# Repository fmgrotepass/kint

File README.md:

# Project moved to [Pillz Mod](https://github.com/dcpedit/pillzmod)

This project has been replaced by Pillz Mod: https://github.com/dcpedit/pillzmod

# KinT Blackpill Edition

This is a fork of Michael Stapelberg's [KinT project](https://github.com/kinx-project/kint) with the following modifications:

* Replaced Teensy with STM32F411 Blackpill controller (`blackpill` directory)
* Reduced PCB size to 100 x 86 mm
* Use Vial firmware.  Source code is in my [fork of Vial](https://github.com/dcpedit/vial-qmk-dev/tree/vial/keyboards/dcpedit/kint_bp)

## Files for JLCPCB
Located in the directory `/blackpill/production`

## Parts for Build
| Component              | Qty | Notes |
| ---------              | --- | ----- |
| SMD LEDs               | 4   | Can be any color [Link](https://octopart.com/apt3216qbc%2Fd-kingbright-5355642?r=sp)
| SMD 10k resistors      | 4   | [Link](https://octopart.com/crcw120610k0fkeac-vishay-20811529)
| Molex 13 pin connectors| 4-6 | Needed if you don't want to desolder old ones [Link](https://octopart.com/39-53-2135-molex-7670149?r=sp)
| STM32F411 Blackpill    | 1   | AliExpress [Link](https://www.aliexpress.us/item/3256801269871873.html)
| Panel mount USB-C      | 1   | Amazon [Link](https://a.co/d/cRoqHqx)
| Socketed headers       |     | Only needed if you want to socket your Blackpill.

## Bluetooth + ZMK build
You can now use the Pillbug dev board along with ZMK firware to make this a wireless mod.  Basically, just swap out the Blackpill with a Pillbug and add a battery.

| Component              | Qty | Notes |
| ---------              | --- | ----- |
| Pillbug                | 1   | MechWild [Link](https://mechwild.com/product/pillbug/)
| 2000 mAh battery       | 1   | Amazon [Link](https://a.co/d/hlTVT1p)

v2022-08-05 of the PCB requires you to bridge the 3.3v pins with a wire.  You can do this easily after soldering the controller in place and tacking a short wire with stripped ends to the existing solder joints on the same side as the LEDs/resistors.  The diagram below shows you which pins.

The current version in the repo does not require this.

If you're using a battery that's larger than 500 mAh, short JP1 on the back of the Pillbug to enable "Charge Boost" (changes charge rate from 100mA to 500mA)

## Firmware
### Vial
Source: https://github.com/dcpedit/vial-qmk-dev/tree/vial/keyboards/dcpedit/kint_bp
* `/firmware/dcpedit_kint_bp_vial.bin` - Default keymap (stock Kinesis)
* `/firmware/dcpedit_kint_bp_vial_6layers.bin` - Support for 6 layers

### ZMK
Source: https://github.com/dcpedit/zmk/tree/kinesispb/app/boards/shields/kinesispb
* `/firmware/zmk_default.uf2` - Default keymap (stock Kinesis)
* `/firmware/zmk_reset.uf2` - Resets PillBug board for BT connectivity issue on MacOS

### Flashing firmware under Linux
The file firmware/dcpedit_kint_bp_vial.bin (or other) can simply be flashed to the Blackpill using the dfu_util. The dfu_util tool requires root privileges if settings are not accessible by the user.

Connect Blackpill to your Linux PC via USB C cable and start unit in DFU mode by holding bootp button and pressing reset button. Wait a second and release the bootp button.

Check the DFU devices by running
```
dfu-util -l
```
The Blackpill device should be visible.

Write the firmware to the device with
```
dfu-util -d 0483:df11 -a 0 -s 0x08000000 -D [PATH TO kint]/firmware/dcpedit_kint_bp_vial.bin
```

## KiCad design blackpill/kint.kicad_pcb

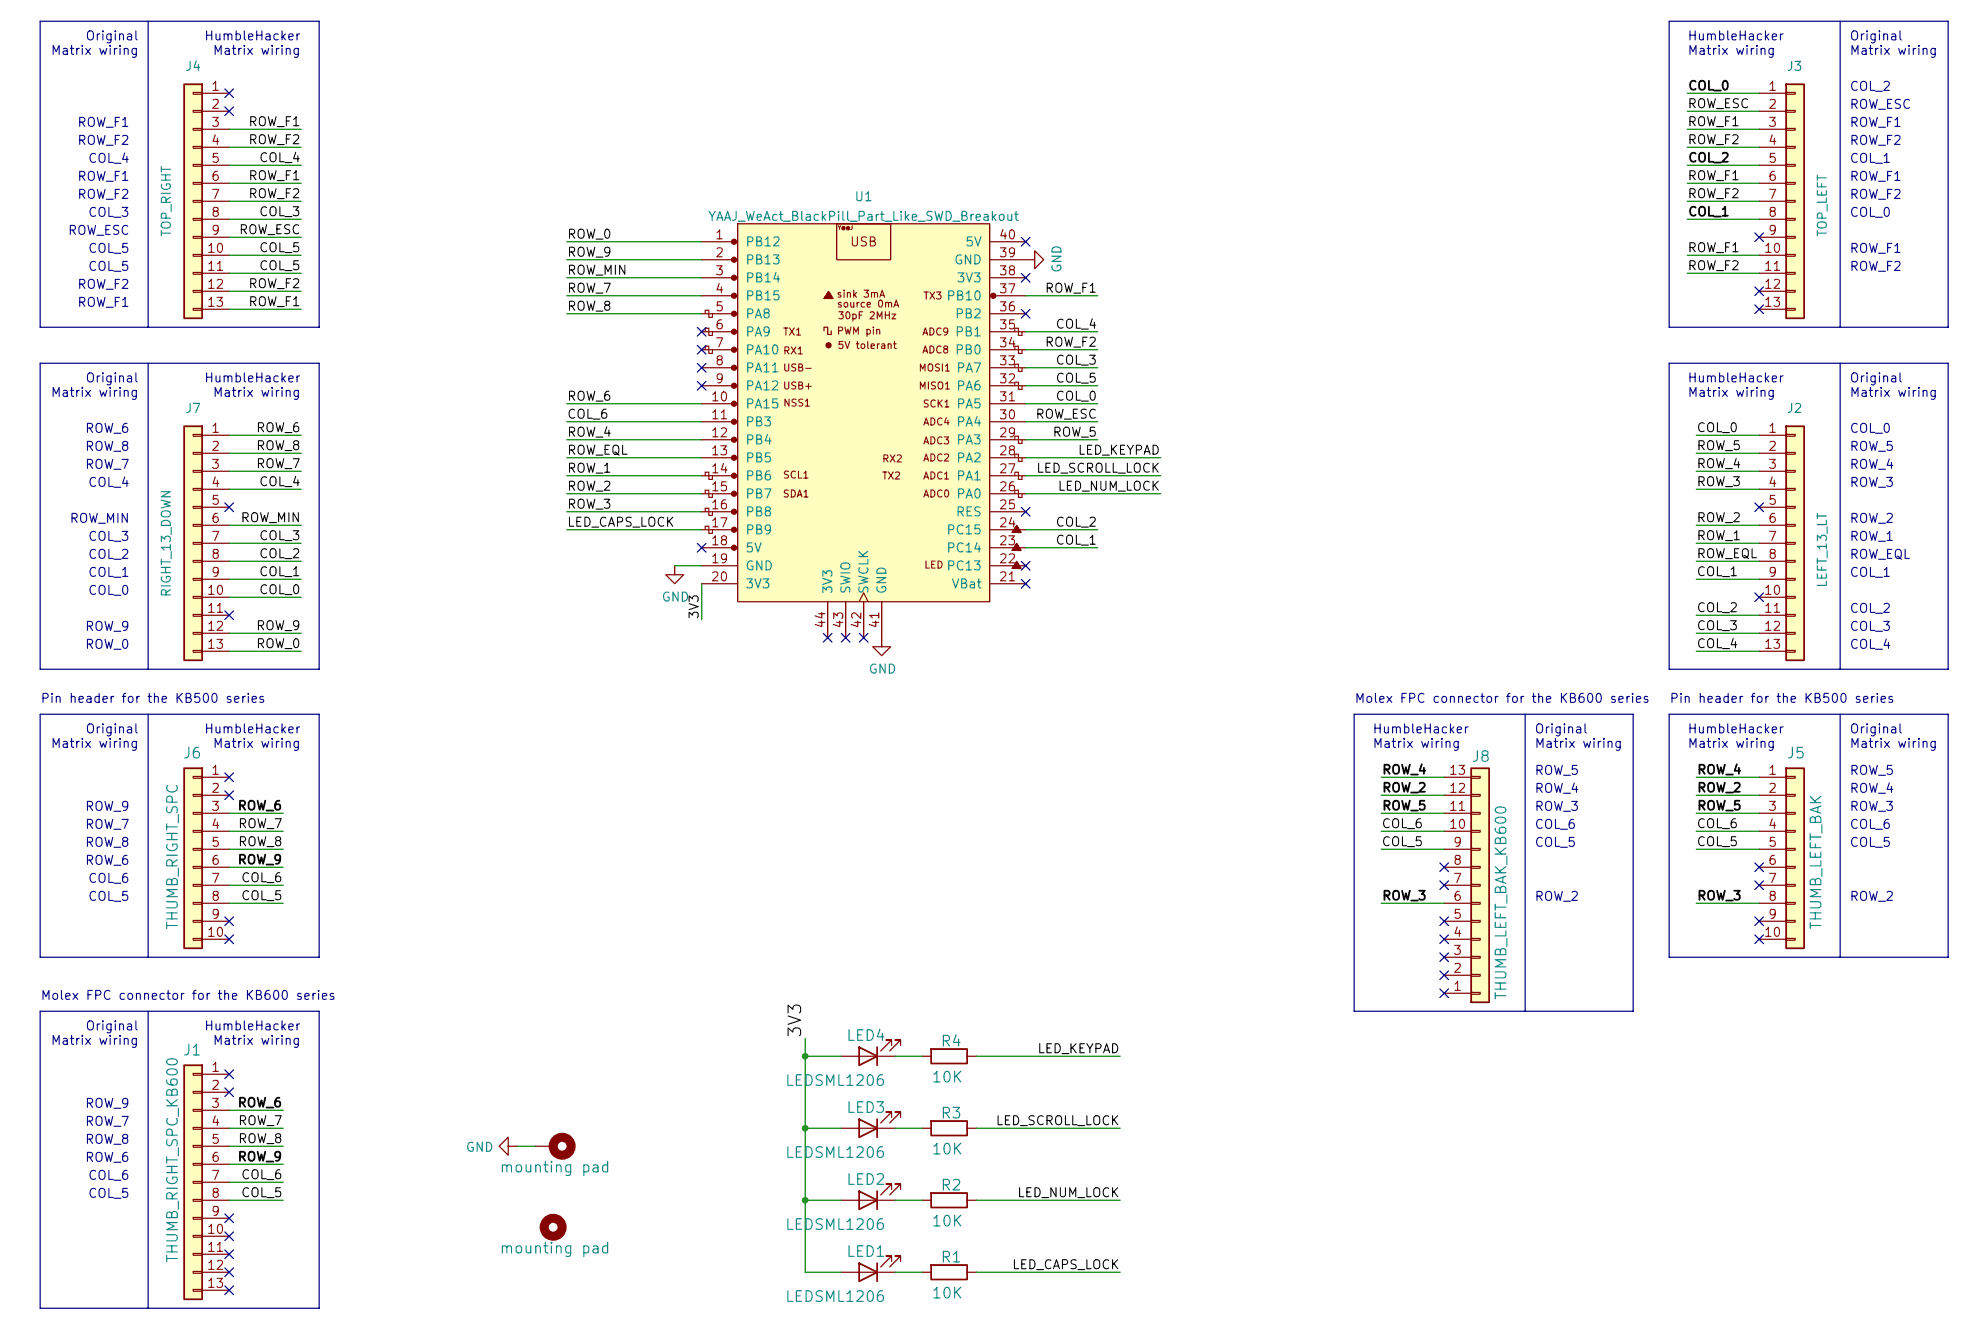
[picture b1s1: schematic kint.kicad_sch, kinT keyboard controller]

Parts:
H1: mounting pad; MountingHole_4.3mm_M4_Pad
H2: mounting pad; MountingHole_6mm
J1: THUMB_RIGHT_SPC_KB600; 39-53-2135; MPN 39-53-2135; digikeypn WM14526-ND
J2: LEFT_13_LT; 39-53-2135; MPN 39-53-2135; digikeypn WM14526-ND
J3: TOP_LEFT; 39-53-2135; MPN 39-53-2135; digikeypn WM14526-ND
J4: TOP_RIGHT; 39-53-2135; MPN 39-53-2135; digikeypn WM14526-ND
J5: THUMB_LEFT_BAK; PinHeader_1x10_P2.54mm_Vertical; MPN 39-53-2135; digikeypn WM14526-ND
J6: THUMB_RIGHT_SPC; PinHeader_1x10_P2.54mm_Vertical; MPN 39-53-2135; digikeypn WM14526-ND
J7: RIGHT_13_DOWN; 39-53-2135; MPN 39-53-2135; digikeypn WM14526-ND
J8: THUMB_LEFT_BAK_KB600; 39-53-2135; MPN 39-53-2135; digikeypn WM14526-ND
LED1, LED2, LED3, LED4: LEDSML1206; LED_1206_3216Metric_Pad1.42x1.75mm_HandSolder; MPN APT3216QBC/D; digikeypn 754-1439-1-ND
R1, R2, R3, R4: 10K; R_1206_3216Metric_Pad1.42x1.75mm_HandSolder; MPN CRCW120610K0FKEAC; digikeypn 541-3983-1-ND
U1: YAAJ_WeAct_BlackPill_Part_Like_SWD_Breakout; YAAJ_WeAct_BlackPill_SWD_2

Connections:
/3V3: LED1.2 (A), LED2.2 (A), LED3.2 (A), LED4.2 (A), U1.20 (3V3)
/COL_0: J2.1, J3.1, J7.10, U1.31 (PA5)
/COL_1: J2.9, J3.8, J7.9, U1.23 (PC14)
/COL_2: J2.11, J3.5, J7.8, U1.24 (PC15)
/COL_3: J2.12, J4.8, J7.7, U1.33 (PA7)
/COL_4: J2.13, J4.5, J7.4, U1.35 (PB1)
/COL_5: J1.8, J4.10, J4.11, J5.5, J6.8, J8.9, U1.32 (PA6)
/COL_6: J1.7, J5.4, J6.7, J8.10, U1.11 (PB3)
/LED_CAPS_LOCK: R1.1, U1.17 (PB9)
/LED_KEYPAD: R4.1, U1.28 (PA2)
/LED_NUM_LOCK: R2.1, U1.26 (PA0)
/LED_SCROLL_LOCK: R3.1, U1.27 (PA1)
/ROW_0: J7.13, U1.1 (PB12)
/ROW_1: J2.7, U1.14 (PB6)
/ROW_2: J2.6, J5.2, J8.12, U1.15 (PB7)
/ROW_3: J2.4, J5.8, J8.6, U1.16 (PB8)
/ROW_4: J2.3, J5.1, J8.13, U1.12 (PB4)
/ROW_5: J2.2, J5.3, J8.11, U1.29 (PA3)
/ROW_6: J1.3, J6.3, J7.1, U1.10 (PA15)
/ROW_7: J1.4, J6.4, J7.3, U1.4 (PB15)
/ROW_8: J1.5, J6.5, J7.2, U1.5 (PA8)
/ROW_9: J1.6, J6.6, J7.12, U1.2 (PB13)
/ROW_EQL: J2.8, U1.13 (PB5)
/ROW_ESC: J3.2, J4.9, U1.30 (PA4)
/ROW_F1: J3.3, J3.6, J3.10, J4.3, J4.6, J4.13, U1.37 (PB10)
/ROW_F2: J3.4, J3.7, J3.11, J4.4, J4.7, J4.12, U1.34 (PB0)
/ROW_MIN: J7.6, U1.3 (PB14)
GND: H1.1, U1.19 (GND), U1.39 (GND), U1.41 (GND)
unnamed: LED1.1 (K), R1.2
unnamed: LED2.1 (K), R2.2
unnamed: LED3.1 (K), R3.2
unnamed: LED4.1 (K), R4.2

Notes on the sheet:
COL_6
ROW_F2
ROW_6
Pin header for the KB500 series
Molex FPC connector for the KB600 series
ROW_7
COL_3
ROW_4
ROW_ESC
COL_0
ROW_3
ROW_2
ROW_1
Original Matrix wiring
ROW_5
ROW_MIN
ROW_F1
HumbleHacker Matrix wiring
ROW_EQL
ROW_9
COL_4
COL_5
COL_1
COL_2
ROW_8
ROW_0

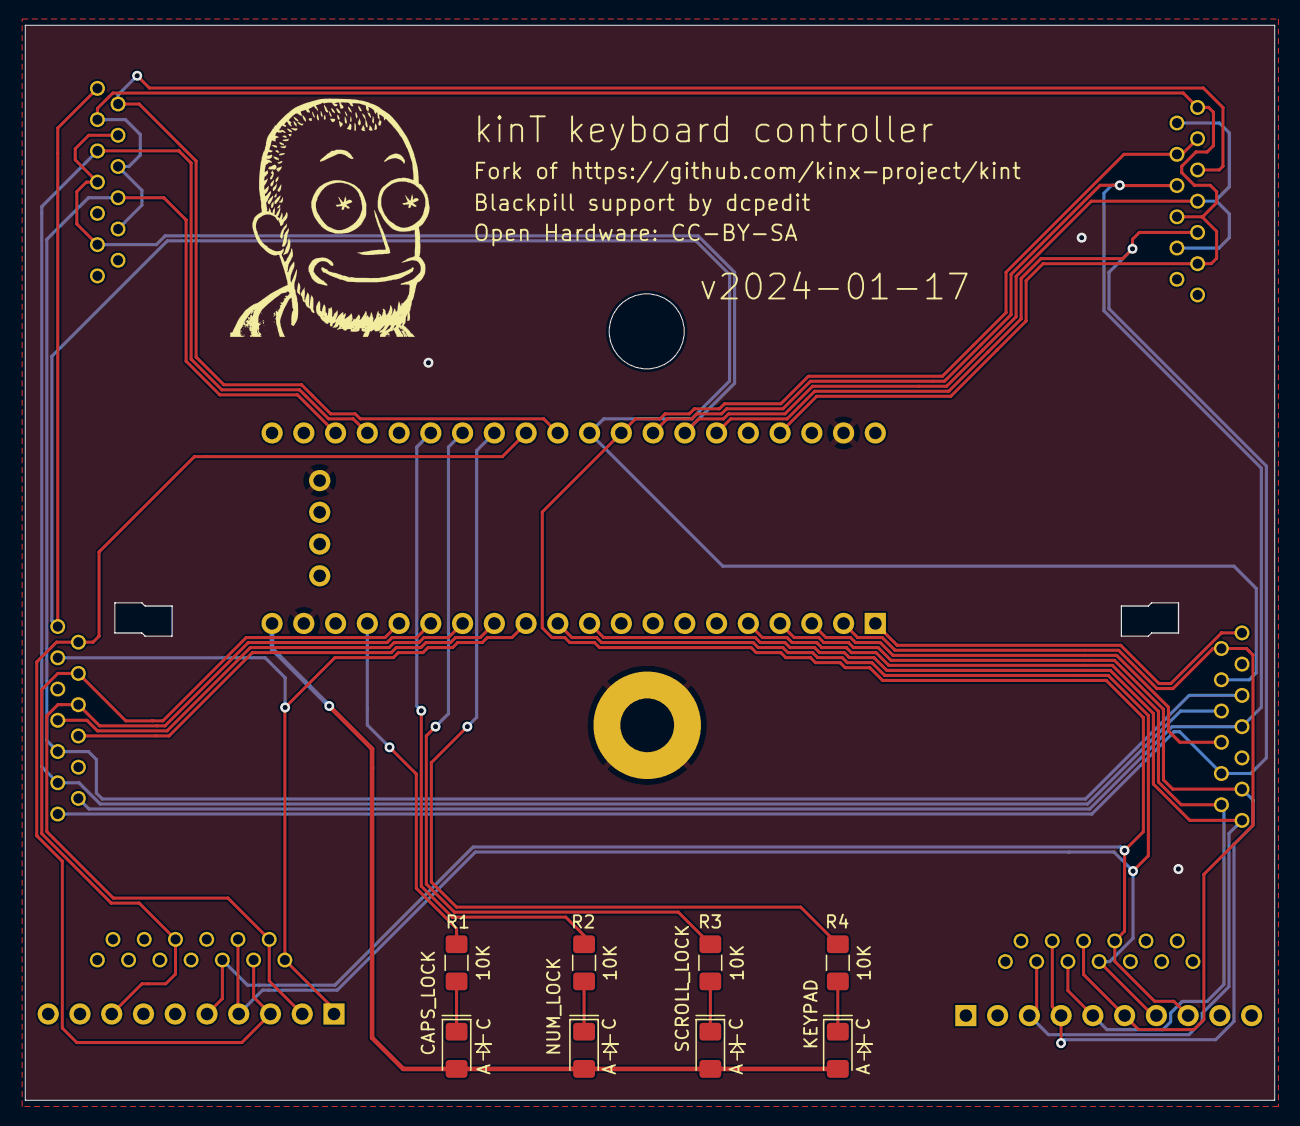
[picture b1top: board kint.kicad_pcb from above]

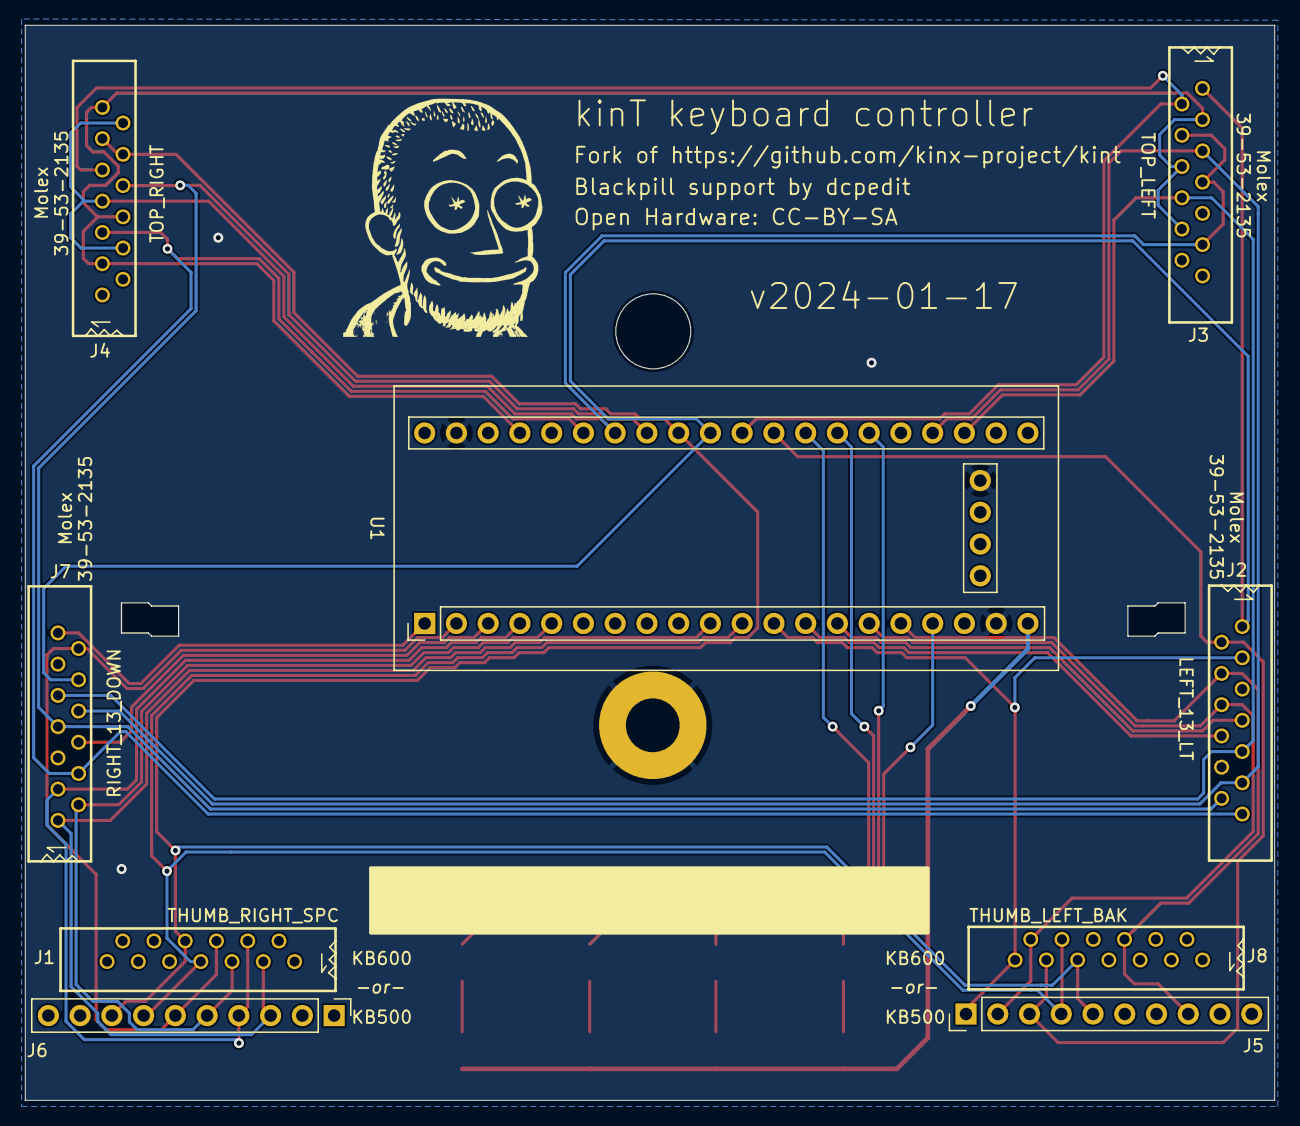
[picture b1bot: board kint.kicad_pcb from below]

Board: 2 copper layers, 99.9 x 86.0 mm, 19 parts (9 on the bottom side), 32 nets.

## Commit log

2022-08-19 Blackpill support
2022-08-22 Update readme. Add firmware
2022-08-26 Add build parts
2023-11-03 Update README.md source link
2023-12-13 Update usb-c link
2023-12-16 Add 6 layer firmware
2024-01-17 Update to remove the need to connect center pins
2024-01-17 Regenerate jlcpcb files
2024-01-17 Add firmware
2024-01-17 Add firmware source links
2024-01-17 Update README.md with wire bridge
2024-04-12 Pillz Mod update
2024-04-12 Fix link
2024-08-03 Add Linux flash procedure to the README.md
2024-08-03 Fix typo's
2024-08-03 Fix more typo's

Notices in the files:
blackpill/kint.kicad_pcb:
Open Hardware: CC-BY-SA
